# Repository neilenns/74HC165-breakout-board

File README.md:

# 74HC165 breakout board

This PCB provides access to the inputs of four serially connected 74HC165s. It's perfect for expanding the number
of inputs available on smaller Arduinos like the Pro Micro or Nano when building flight simulator components
that interact with [MobiFlight](http://www.mobiflight.com).

## Ordering from JLCPCB

These boards are ready to order from JLCPCB with their SMT fabrication service. You'll receive boards with all
the components soldered on except for the pin headers which you add yourself.

### Setting up the PCB details

1. Download and unpack `74HC165-breakout-board-JLCPCB.zip` from [the latest release](https://github.com/neilenns/74HC165-breakout-board/releases/latest). You will wind up with three files:

   - `74HC165-breakout-board-JLCPCB.zip`
   - `74HC165-breakout-board_bom_jlc.csv`
   - `74HC165-breakout-board_cpl_jlc.csv`

2. Start a new order with JLCPCB and upload the `74HC165-breakout-board-JLCPCB.zip` file for the Gerbers.
3. Set the `Surface Finish` option to `LeadFree HASL-RoHS`.
4. Set the `Remove Order Number` option to `Specify a location`.
5. Enable the `SMT Assembly` option.
6. Make sure `Assemble top side` is selected.
7. Set the `Tooling holes` option to `Added by customer`.
8. Agree to the terms and select the `Confirm` button.

### Setting up the SMT assembly

1. Upload the `74HC165-breakout-board_bom_jlc.csv` file for the BOM file.
2. Upload the `74HC165-breakout-board_bom_jlc` file for the CPL file.
3. Select the `Next` button.
4. Verify three parts are detected: `4D03WGJ0103T5E`, `CC0805KRX7R9BB104` and `74HC165D,653`. If you are ordering the default 5 boards
   you'll see order quantities of 50 for each part due to minimum part count requirements. This is expected.
5. Select the `Next` button.
6. Select the `Save to cart` button.

The total cost for five green PCBs with all parts assembled should be around $16.

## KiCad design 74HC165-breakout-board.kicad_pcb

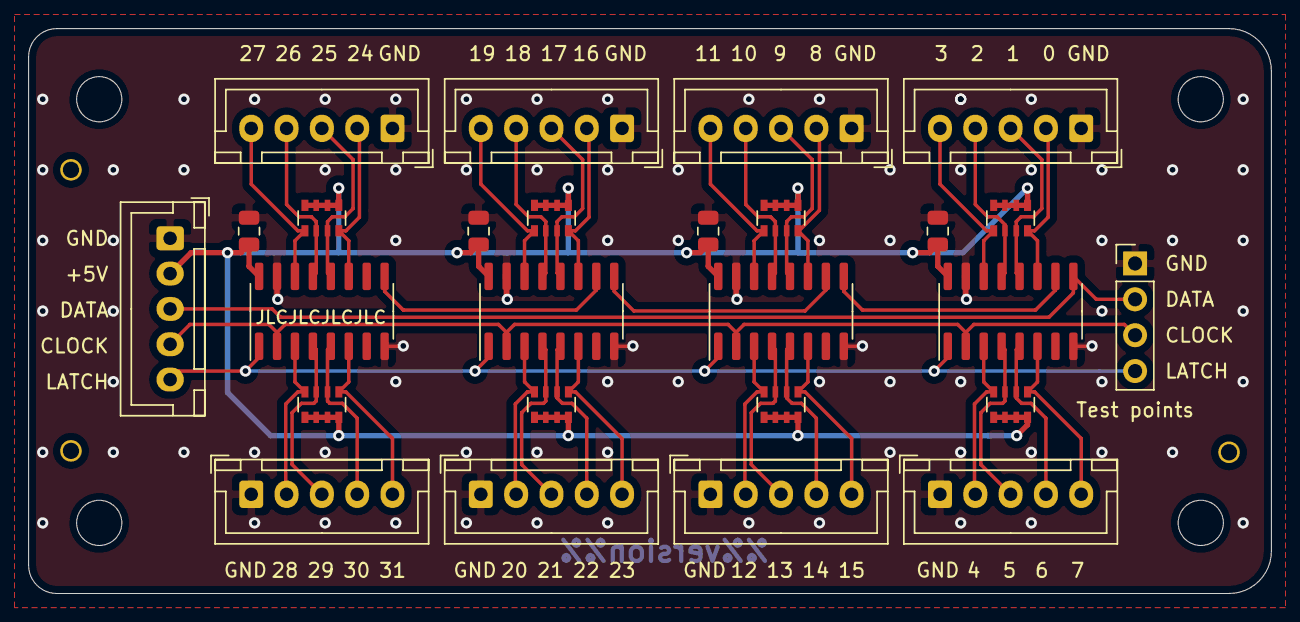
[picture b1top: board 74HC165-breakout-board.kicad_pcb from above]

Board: 2 copper layers, 88.0 x 40.0 mm, 33 parts (0 on the bottom side), 40 nets.

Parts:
C1, C2, C3, C4: 100nF; C_0805_2012Metric
H1, H2, H3, H4: MountingHole; MountingHole_3.2mm_M3
H5, H6, H7: MountingHole; JLCPCB_Tooling_Hole
J1, J2, J3, J4, J5, J6, J7, J8, J9: Conn_01x05; JST_XH_B5B-XH-A_1x05_P2.50mm_Vertical
J10: Conn_01x04; PinHeader_1x04_P2.54mm_Vertical
RN1, RN2, RN3, RN4, RN5, RN6, RN7, RN8: R_Pack04; R_Array_Convex_4x0603
U1, U2, U3, U4: 74HC165; SOIC-16_3.9x9.9mm_P1.27mm

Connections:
+5V: C1.1, C2.1, C3.1, C4.1, J1.2, RN1.1, RN1.2, RN1.3, RN1.4, RN2.1, RN2.2, RN2.3, RN2.4, RN3.1, RN3.2, RN3.3, RN3.4, RN4.1, RN4.2, RN4.3, RN4.4, RN5.1, RN5.2, RN5.3, RN5.4, RN6.1, RN6.2, RN6.3, RN6.4, RN7.1, RN7.2, RN7.3, RN7.4, RN8.1, RN8.2, RN8.3, RN8.4, U1.16, U2.16, U3.16, U4.16
/74HC165/A: J2.2, RN1.8, U1.11
/74HC165/B: J2.3, RN1.7, U1.12
/74HC165/C: J2.4, RN1.6, U1.13
/74HC165/D: J2.5, RN1.5, U1.14
/74HC165/E: J3.2, RN2.8, U1.3
/74HC165/F: J3.3, RN2.7, U1.4
/74HC165/G: J3.4, RN2.6, U1.5
/74HC165/H: J3.5, RN2.5, U1.6
/74HC165/QH: U1.9, U2.10
/sheet61DDC3C2/A: J6.2, RN5.8, U3.11
/sheet61DDC3C2/B: J6.3, RN5.7, U3.12
/sheet61DDC3C2/C: J6.4, RN5.6, U3.13
/sheet61DDC3C2/D: J6.5, RN5.5, U3.14
/sheet61DDC3C2/E: J7.2, RN6.8, U3.3
/sheet61DDC3C2/F: J7.3, RN6.7, U3.4
/sheet61DDC3C2/G: J7.4, RN6.6, U3.5
/sheet61DDC3C2/H: J7.5, RN6.5, U3.6
/sheet61DDC3C2/QH: U3.9, U4.10
/sheet61DDC5EC/A: J8.2, RN7.8, U4.11
/sheet61DDC5EC/B: J8.3, RN7.7, U4.12
/sheet61DDC5EC/C: J8.4, RN7.6, U4.13
/sheet61DDC5EC/D: J8.5, RN7.5, U4.14
/sheet61DDC5EC/E: J9.2, RN8.8, U4.3
/sheet61DDC5EC/F: J9.3, RN8.7, U4.4
/sheet61DDC5EC/G: J9.4, RN8.6, U4.5
/sheet61DDC5EC/H: J9.5, RN8.5, U4.6
/sheet61DDC16C/A: J4.2, RN3.8, U2.11
/sheet61DDC16C/B: J4.3, RN3.7, U2.12
/sheet61DDC16C/C: J4.4, RN3.6, U2.13
/sheet61DDC16C/D: J4.5, RN3.5, U2.14
/sheet61DDC16C/E: J5.2, RN4.8, U2.3
/sheet61DDC16C/F: J5.3, RN4.7, U2.4
/sheet61DDC16C/G: J5.4, RN4.6, U2.5
/sheet61DDC16C/H: J5.5, RN4.5, U2.6
/sheet61DDC16C/QH: U2.9, U3.10
CLOCK: J1.4, J10.3, U1.2, U2.2, U3.2, U4.2
DATA: J1.3, J10.2, U4.9
GND: C1.2, C2.2, C3.2, C4.2, J1.1, J2.1, J3.1, J4.1, J5.1, J6.1, J7.1, J8.1, J9.1, J10.1, U1.8, U1.15, U2.8, U2.15, U3.8, U3.15, U4.8, U4.15
LATCH: J1.5, J10.4, U1.1, U2.1, U3.1, U4.1

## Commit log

2022-01-10 Initial version
2022-01-10 Add GND to each header, remove daisy chain
2022-01-10 Switch to footprints available at JLCPCB
2022-01-10 Fix resistors, add tooling holes, add test points
2022-01-10 Add PCB measurements
2022-01-10 Add ordering information to the readme
2022-01-10 Add version and date stamps
2022-01-10 Fix error in release script
2022-01-10 Attempt to disable date reformatting
2022-01-10 Try changing Docker image
2022-01-10 Revert back to old release.yml file
2022-01-10 Remove date reformat
2022-01-10 Try moving a bracket?
2022-01-10 Get rid of date and version from PCB page settings, add MF logo
2022-01-10 Try putting quotes around the date
2022-01-10 Actually quote the string
2022-01-11 Add date and version back to PCB
2022-01-11 Add date back to PCB silkscreen
2022-01-11 Add 3d renders
2022-01-11 Put ground on pin 1 of all the connectors Fixes #1
2022-01-11 Add pin numbers to back of board Fixes #3
2022-01-11 Make board previews MobiFlight blue Fixes #7
2022-01-11 Add via stitching Fixes #4
2022-01-11 Include an ORDERING.md file with releases Fixes #10
2022-01-11 Revert "Merge pull request #11 from neilenns:neilenns/issue10"
    This reverts commit d66564c554acaec69eb6108aa00bc893de5022c0, reversing
    changes made to 3f49475d56eaa1cc92ed6001720ee4fcf3f05b14.
2022-01-12 Update readme with links to latest release and pictures Fixes #13
2025-02-25 Add renovate.json
